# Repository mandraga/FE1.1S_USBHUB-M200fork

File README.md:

# FE1.1S_USBHUB

## Description:
This is an working USB HUB using the FE1.1S ic. It has low transfer speed, but it\`s working.<br>
The board has 5 led\`s(one to show each port activity and one for general working), 4 decoupling capacitors (for the 1.8V, 3.3V and 5V internal regulators), an 2.7kohm (+- 1%) resistor between pin 14 and GND and an  12MHz oscilator between pins 2 and 3.

<table>
  <tr>
    <td></td>
    <td></td>
  </tr>
</table>

## My schematic

## Results:
As you can see, the USB hub is recognised and it\`s working. 
One ["mistake"](https://github.com/Tonikiller10000/FE1.1S_USBHUB/blob/main/Usb_Hub_Pictures/12.jpg) I connected the GND trouth the USB ports mounting pins, witch needs that all the ports to be connected, or to connect the mounting boles of the ports with an wire.
The thing I don\`t like is it\`s transfer speed, but in the future I think I can experiment with it to make it work at the USB2.0 full speed(480MHz) and to use it`s pins to be controlled by a microcontroller.

## Links:
- FE1.1sDatasheet: https://cdn-shop.adafruit.com/product-files/2991/FE1.1s%20Data%20Sheet%20(Rev.%201.0).pdf
- The schematic from witch I did mine: https://github.com/Tonikiller10000/FE1.1S_USBHUB/blob/main/Usb_Hub_Pictures/3.png

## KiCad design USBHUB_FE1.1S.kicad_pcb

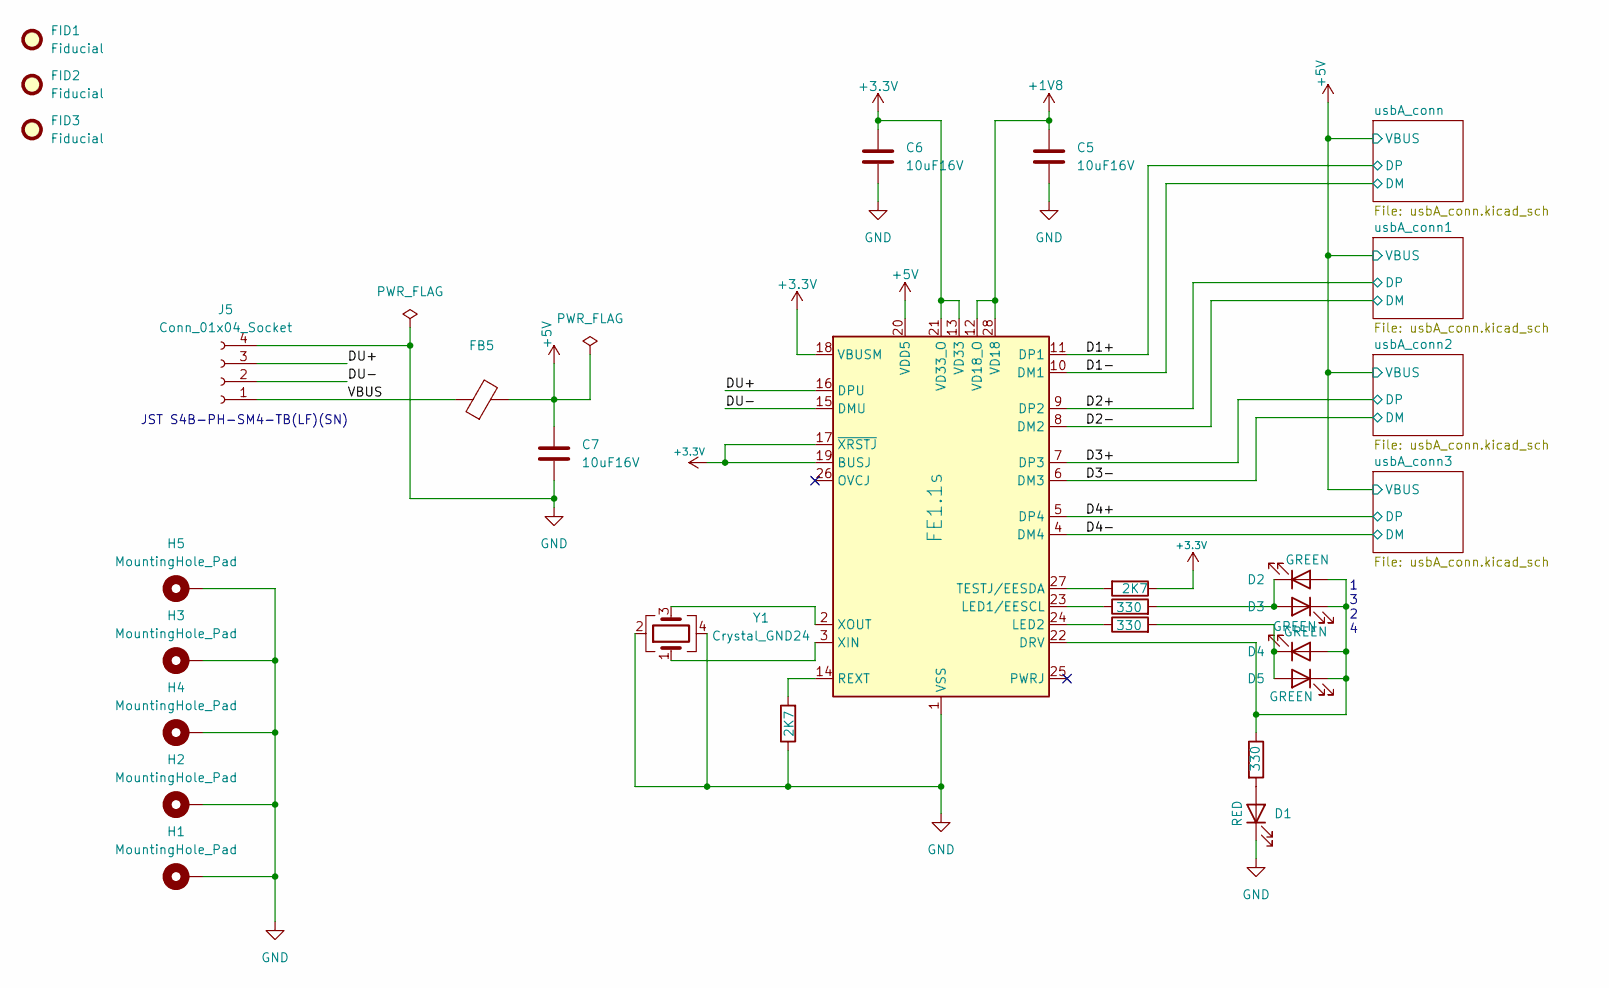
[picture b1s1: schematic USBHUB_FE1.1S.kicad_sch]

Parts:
C5, C6, C7: 10uF16V; C_0805_2012Metric
D1: RED; LED_0805_2012Metric
D2, D3, D4, D5: GREEN; LED_0805_2012Metric
FB5: FerriteBead; L_0805_2012Metric; FarnellRef 2800851RL
FID1, FID2, FID3: Fiducial; Fiducial_0.5mm_Mask1.5mm
H1, H2, H3, H4, H5: MountingHole_Pad; MountingHole_3.2mm_M3_DIN965_Pad_TopBottom
J5: Conn_01x04_Socket; JST_PH_S4B-PH-SM4-TB_1x04-1MP_P2.00mm_Horizontal; FarnellRef 9492631
R1, R4, R5: 330; R_0805_2012Metric
R2, R3: 2K7; R_0805_2012Metric
U1: FE1.1s; SSOP-28_3.9x9.9mm_P0.635mm
Y1: Crystal_GND24; Crystal_SMD_3225-4Pin_3.2x2.5mm; FarnellRef 2853914RL

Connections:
+1V8: C5.1, U1.12 (VD18_O), U1.28 (VD18)
+3.3V: C6.1, R2.1, U1.13 (VD33), U1.17 (~XRSTJ), U1.18 (VBUSM), U1.19 (BUSJ), U1.21 (VD33_O)
+5V: C7.1, FB5.2, U1.20 (VDD5); also elsewhere on the board
/D1+: U1.11 (DP1); also elsewhere on the board
/D1-: U1.10 (DM1); also elsewhere on the board
/D2+: U1.9 (DP2); also elsewhere on the board
/D2-: U1.8 (DM2); also elsewhere on the board
/D3+: U1.7 (DP3); also elsewhere on the board
/D3-: U1.6 (DM3); also elsewhere on the board
/D4+: U1.5 (DP4); also elsewhere on the board
/D4-: U1.4 (DM4); also elsewhere on the board
/DU+: J5.3, U1.16 (DPU)
/DU-: J5.2, U1.15 (DMU)
/VBUS: FB5.1, J5.1
GND: C5.2, C6.2, C7.2, D1.1 (K), H1.1, H2.1, H3.1, H4.1, H5.1, J5.4, R3.1, U1.1 (VSS), Y1.2, Y1.4; also elsewhere on the board
unnamed: D1.2 (A), R1.2
unnamed: D2.2 (A), D3.1 (K), D4.2 (A), D5.1 (K), R1.1, U1.22 (DRV)
unnamed: D2.1 (K), D3.2 (A), R4.2
unnamed: D4.1 (K), D5.2 (A), R5.2
unnamed: R4.1, U1.23 (LED1/EESCL)
unnamed: R5.1, U1.24 (LED2)
unnamed: R3.2, U1.14 (REXT)
unnamed: R2.2, U1.27 (TESTJ/EESDA)
unnamed: U1.3 (XIN), Y1.1
unnamed: U1.2 (XOUT), Y1.3

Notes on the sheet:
1 3 2 4
JST S4B-PH-SM4-TB(LF)(SN)

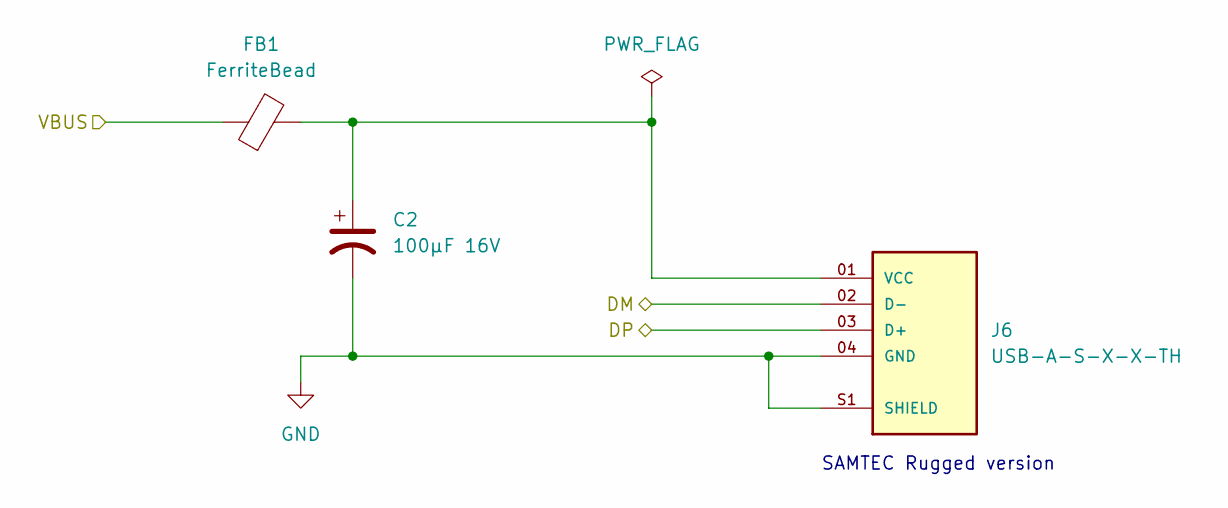
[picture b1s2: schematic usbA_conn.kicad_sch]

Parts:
C2: 100µF 16V; CP_Elec_6.3x5.4; FarnellRef 2611356
FB1: FerriteBead; L_0805_2012Metric; FarnellRef 2800851RL
J6: USB-A-S-X-X-TH; SAMTEC_USB-A-S-X-X-TH; PARTREV R

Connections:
+5V: FB1.1; also elsewhere on the board
/D1+: J6.03 (D+); also elsewhere on the board
/D1-: J6.02 (D-); also elsewhere on the board
GND: C2.2, J6.04 (GND), J6.S1 (SHIELD), J6.S2 (SHIELD); also elsewhere on the board

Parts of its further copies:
C1, C3, C4: 100µF 16V; CP_Elec_6.3x5.4; FarnellRef 2611356
FB2, FB3, FB4: FerriteBead; L_0805_2012Metric; FarnellRef 2800851RL
J7, J8, J9: USB-A-S-X-X-TH; SAMTEC_USB-A-S-X-X-TH; PARTREV R

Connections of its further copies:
+5V: FB2.1, FB3.1, FB4.1; also elsewhere on the board
/D2+: J7.03 (D+); also elsewhere on the board
/D2-: J7.02 (D-); also elsewhere on the board
/D3+: J8.03 (D+); also elsewhere on the board
/D3-: J8.02 (D-); also elsewhere on the board
/D4+: J9.03 (D+); also elsewhere on the board
/D4-: J9.02 (D-); also elsewhere on the board
GND: C1.2, C3.2, C4.2, J7.04 (GND), J7.S1 (SHIELD), J7.S2 (SHIELD), J8.04 (GND), J8.S1 (SHIELD), J8.S2 (SHIELD), J9.04 (GND), J9.S1 (SHIELD), J9.S2 (SHIELD); also elsewhere on the board
unnamed: C3.1, FB3.2, J8.01 (VCC)
unnamed: C4.1, FB4.2, J9.01 (VCC)

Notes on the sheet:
SAMTEC Rugged version

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
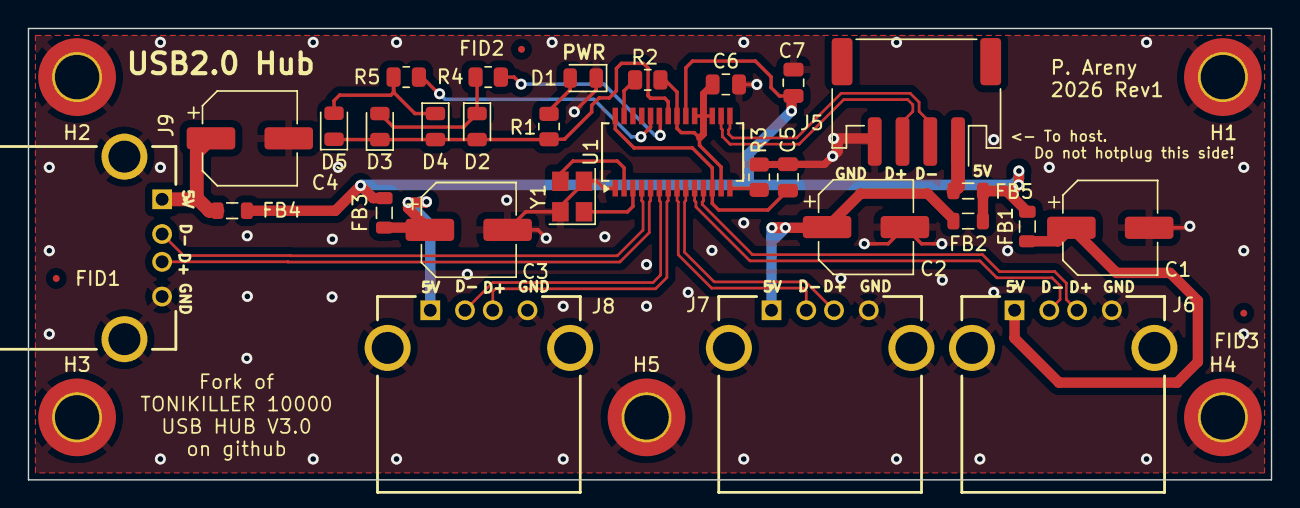
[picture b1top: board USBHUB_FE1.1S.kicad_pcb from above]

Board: 2 copper layers, 89.5 x 32.5 mm, 37 parts (0 on the bottom side), 29 nets.

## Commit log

2026-02-16 Adds capacitors and ferrite beads
    Also a Fatrnell BOM.
2026-02-17 Finished schematic
    The USB-A connector foortprint, 3D model, and symbol comes from Snap
    EDA.
2026-02-17 ERC pass but one ground pin on th eUSB-A connector.
2026-02-17 Routed, Rev1
2026-02-17 Reordering the leds on the board.
    They should be in the same order as the ports.
2026-02-19 Puts port on the side
